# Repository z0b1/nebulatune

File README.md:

# NebulaTune

NebulaTune is a HF reciever utilizng a Direct Conversion Single Balanced Diode Product Detector along with an RP2350 to display and choose frequency and recieve with an digital encoder!

## Preview

---
# Lapse link
[View Timelapses](https://lapse.hackclub.com/timelapse/dcauUObcYn6o/)
---
# Demo

##  - link to the PCB on KiCanvas
##  - link to the SCH on KiCanvas

# Features

- Adjustable VFO with a rotary encoder;
- Frequency display;
- Direct Conversion Single Balanced Diode Product Detector;
- Speaker or headphones output;
- Wide range of frequencies(3-30MHz);
- Local oscillator high stability crystal Si5351 by SiliconLabs;
- SDR and waterfall display soon&trade;.

# DIY How to

1. Analyze the schematic and PCB design and determine if these fit your needs;

2. Gather all of the needed parts from the BOM;

3. A housing is wished for but not needed especially if you plan on tweaking my design;

4. Print the PCB(Only the `F.Cu` and that is in reverse) or order it from JLCPCB(not sponsored);

5. Install the MicroPico extension if using VS Code or just use Thonny;

6. More to come later...

# How it works
 
## General overview

This direct conversion single balanced diode product detector setup is pretty common, it utilizes the Si5351 as the local VFO. That way we eliminate the need for a frequency counter, because the frequency can be set and read with the RP2350!

## Tech details
Now lets get to the core, this direct conversion single balanced diode product detector is similar to Polyakov's mixer which is a small and easy to setup/begginer friendly HF reciever. I took inspo for the 7MHz band design, but with some tweaking the reciever should work on the whole HF band. I choose to make a reciever becuase you don't need a license to listen, and hope to bring more people into Ham Radio. The reason I used the RP2350 is because I hope to make a waterfall and split this into I and Q signals, so I can do ADC on the RP2350 and hopefully make an HF SDR Transciever.

## Explanation

Now, I hope that the reader know what HF and SDR mean, but just in case if someone doesn't know, I will explain the meaning of HF and SDR to you, also some other technical terms I used in this README.
HF just means High Frequency and that is the defined range of frequencies **in this case (3MHz to 30MHz)**. There are also other ranges like VHF, UHF, EHF, SHF and so on!
SDR means Software Defined Radio, that is if your microcontroller/PC analyze the input values of your ADC(Analog to Digital Converter) and visualise it and control the Radio via the Software.

## I'd like to add

I'd like to add although I'm in this hobby for 8 years already, and despite me being a hardware fanatic this is only my second RF project so please contribute and tell me if I have made any mistakes! Also I'm currentley looking for sponsors for my YSWS called **Propagation**!
### Propagation

Propagation is a Hack Club YSWS in production, the idea behind this is that many people have never heard of or tried the magics of RF, our goal is to get people to make projects relating RF, learn about RF and maybe get into the hobby. What separates us from other Radio related YSWS's is that we do not require a license, would be incredible if you have one but our main goal is to expand the use of RF in every sphere of life!
# Credits
Big shoutout to my father, without him, having patience and will to work is getting hard as I easily get annoyed but he gets me to enjoy this, also he's the main finder of other open source projects which I later work on and modify
---
### The idea for using the Si5351
---
[Link to github repository of the inspo for the Si5351.](https://github.com/TeknoTrek/Si5351-Clock-Generator-for-Arduino-Projects)
---
### The idea for the Direct Conversion Single Balanced Diode Product Detector
---
[Link to the Direct Conversion Single Balanced Diode Product Detector.](https://ra1ohx.ru/publ/skhemy_radioljubitelju/priemniki/prostoj_priemnik_prjamogo_preobrazovanija_na_diapazon_7_mgc/13-1-0-153)
---
> Translate the site to english, its in russian.
# Bill Of Materials
---
|Reference|Part|Qty|Price|Total|Description|
|:---|:---:|:---|:---:|:---:|:---:|
|AE1|Antenna|1|3.66E|3.66E|BNC CONNECTOR|
|C1|Capacitor|1|0.3E|0.3E|60|
|C2,C7,C8|Capacitor|3|0.1E|0.3E|10n|
|C3|Capacitor|1|0.15|0.15|470n|
|C4|CP|1|0.2|0.2|22u/10V|
|C5|CP|1|X|X|100u/16V|
|C6|Capacitor|1|X|X|100n|
|D1,D2|Diode|2|X|X|1N4148|
|J1|VFO|1|6.5|6.5|Si5351|
|J2|Display|1|6.8|6.8|OLED 128x64 I2C|
|L1|Inductor/Choke Coupled|1|0.2|0.2|L1 22uH L2 100uH|
|LS1|Speaker|1|2.8|2.8|8Ohm|
|R1|Resistor|1|x|x|1|
|RV1|Trimmer|1|0.2|0.2|1k|
|SW1|Rotary encoder swithch|1|1|1|/|
|U1|TDA2003|1|1.5|1.5|Audio amp|
|U2|XIAO RP2350 DIP|1|9|9|Main MCU|
> Total 32.61 Euros or 37.33 USD, price might vary for shipping and availabilty reasons.

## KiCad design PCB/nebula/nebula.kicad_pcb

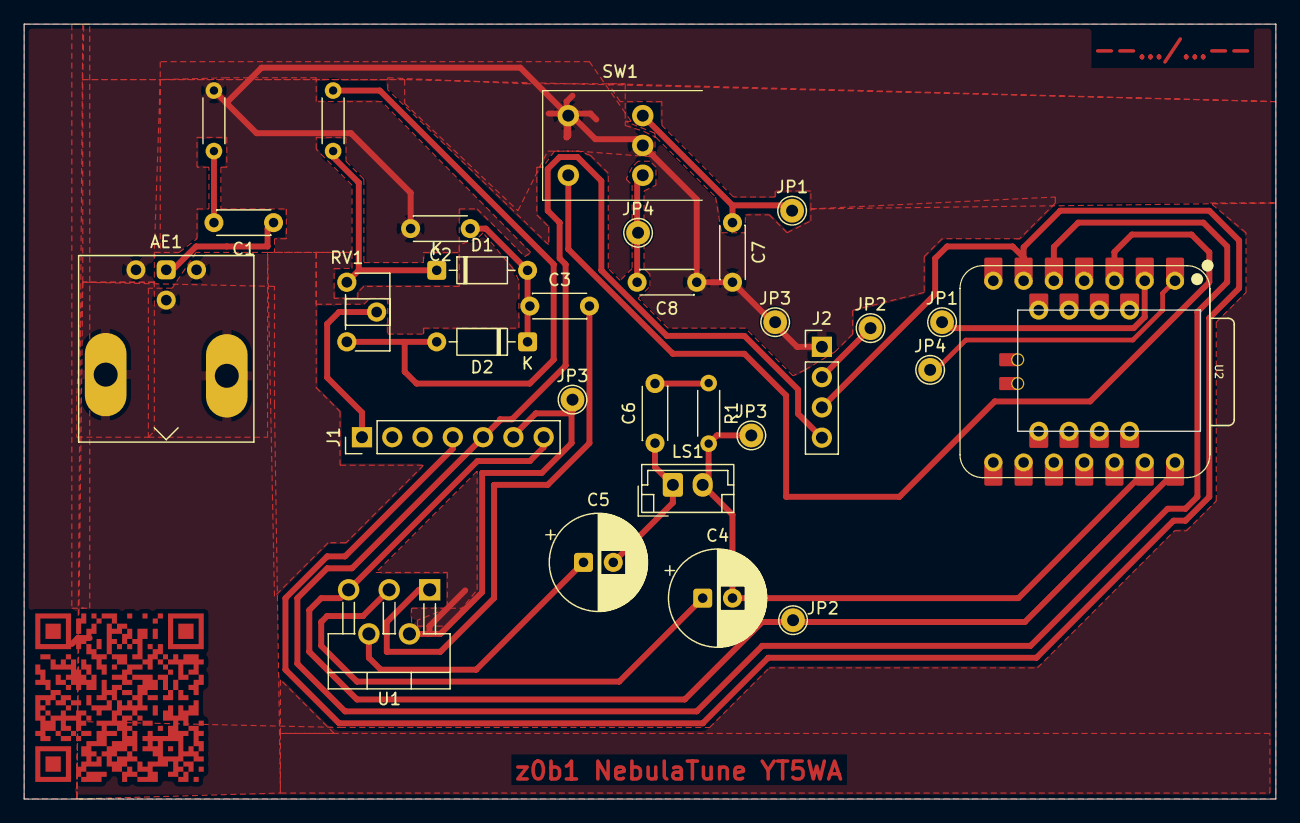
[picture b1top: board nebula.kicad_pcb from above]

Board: 2 copper layers, 105.0 x 65.0 mm, 28 parts (0 on the bottom side), 17 nets.

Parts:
AE1: Antenna; BNC_Amphenol_031-6575_Horizontal
C1: 60; C_Disc_D4.3mm_W1.9mm_P5.00mm
C2, C7, C8: 10n; C_Disc_D4.3mm_W1.9mm_P5.00mm
C3: 470n; C_Disc_D4.3mm_W1.9mm_P5.00mm
C4: 22u/10V; CP_Radial_D8.0mm_P2.50mm
C5: 100u/16V; CP_Radial_D8.0mm_P2.50mm
C6: 100n; C_Disc_D4.3mm_W1.9mm_P5.00mm
D1, D2: 1N4148; D_DO-35_SOD27_P7.62mm_Horizontal
J1: Si5351 Module; PinHeader_1x07_P2.54mm_Vertical
J2: OLED 128x64 I2C; PinHeader_1x04_P2.54mm_Vertical
JP1, JP1#2, JP2, JP2#2, JP3, JP3#2, JP3#3, JP4, JP4#2: TestPoint_THTPad_D2.0mm_Drill1.0mm
LS1: 8Ω; JST_EH_B2B-EH-A_1x02_P2.50mm_Vertical
R1: 1; R_Axial_DIN0204_L3.6mm_D1.6mm_P5.08mm_Horizontal
RV1: 1k; Potentiometer_ACP_CA6-H2,5_Horizontal
SW1: RotaryEncoder_Switch; RotaryEncoder_Bourns_Horizontal_PEC09-2xxxF-Sxxxx
U1: TDA2003; TO-220-5_P3.4x3.7mm_StaggerOdd_Lead3.8mm_Vertical
U2: XIAO-RP2350-DIP

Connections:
+5V: J1.7, J2.2, JP2.1, JP2#2.1, U1.5 (V+), U2.14 (VBUS)
/CLK0: J1.1, RV1.2
/SCL: J1.4, J2.3, U2.6 (D5)
/SDA: J1.5, J2.4, U2.5 (D4)
/SWRT: SW1.S1, U2.3 (D2)
GND: AE1.2, AE1.3, AE1.4, C2.2, C4.2, C7.2, C8.1, J1.6, J2.1, JP3.1, JP3#2.1, JP3#3.1, LS1.2, R1.2, SW1.C, SW1.S2, U1.2 (-), U2.13 (GND)
unnamed: AE1.1 (A_1), C1.1
unnamed: C5.1, U1.4
unnamed: C5.2, C6.1, LS1.1
unnamed: C6.2, R1.1
unnamed: C2.1, C3.1, D1.2 (A), D2.1 (K)
unnamed: D1.1 (K), RV1.1
unnamed: D2.2 (A), RV1.3
unnamed: C3.2, U1.1 (+)
unnamed: C4.1, U1.3 (GND)
unnamed: C8.2, JP4.1, JP4#2.1, SW1.A, U2.1 (D0)
unnamed: C7.1, JP1.1, JP1#2.1, SW1.B, U2.2 (D1)
